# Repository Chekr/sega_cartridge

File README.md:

# sega_cartridge

NOTE: Part datasheets are NOT included with the license, and are included for reference use ONLY

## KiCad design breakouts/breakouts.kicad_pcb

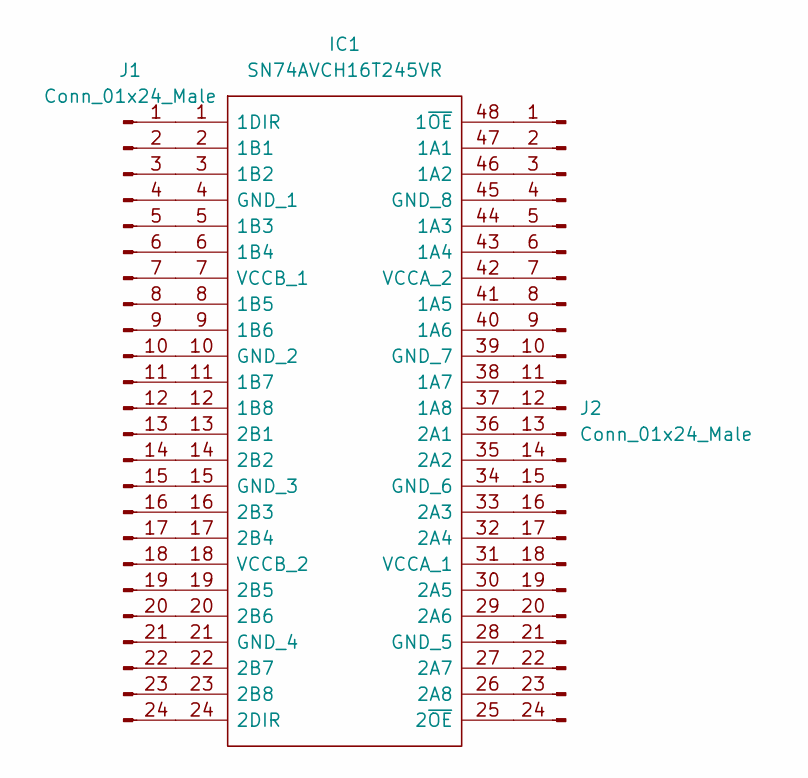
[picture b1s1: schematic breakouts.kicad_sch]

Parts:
IC1: SN74AVCH16T245VR; SOP40P640X120-48N; Manufacturer_Part_Number SN74AVCH16T245VR; Mouser Part Number 595-SN74AVCH16T245VR
J1, J2: Conn_01x24_Male; PinHeader_1x24_P2.54mm_Vertical

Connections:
unnamed: IC1.1 (1DIR), J1.1
unnamed: IC1.2 (1B1), J1.2
unnamed: IC1.3 (1B2), J1.3
unnamed: IC1.4 (GND_1), J1.4
unnamed: IC1.5 (1B3), J1.5
unnamed: IC1.6 (1B4), J1.6
unnamed: IC1.7 (VCCB_1), J1.7
unnamed: IC1.8 (1B5), J1.8
unnamed: IC1.9 (1B6), J1.9
unnamed: IC1.10 (GND_2), J1.10
unnamed: IC1.11 (1B7), J1.11
unnamed: IC1.12 (1B8), J1.12
unnamed: IC1.13 (2B1), J1.13
unnamed: IC1.14 (2B2), J1.14
unnamed: IC1.15 (GND_3), J1.15
unnamed: IC1.16 (2B3), J1.16
unnamed: IC1.17 (2B4), J1.17
unnamed: IC1.18 (VCCB_2), J1.18
unnamed: IC1.19 (2B5), J1.19
unnamed: IC1.20 (2B6), J1.20
unnamed: IC1.21 (GND_4), J1.21
unnamed: IC1.22 (2B7), J1.22
unnamed: IC1.23 (2B8), J1.23
unnamed: IC1.24 (2DIR), J1.24
unnamed: IC1.25 (2~OE), J2.24
unnamed: IC1.26 (2A8), J2.23
unnamed: IC1.27 (2A7), J2.22
unnamed: IC1.28 (GND_5), J2.21
unnamed: IC1.29 (2A6), J2.20
unnamed: IC1.30 (2A5), J2.19
unnamed: IC1.31 (VCCA_1), J2.18
unnamed: IC1.32 (2A4), J2.17
unnamed: IC1.33 (2A3), J2.16
unnamed: IC1.34 (GND_6), J2.15
unnamed: IC1.35 (2A2), J2.14
unnamed: IC1.36 (2A1), J2.13
unnamed: IC1.37 (1A8), J2.12
unnamed: IC1.38 (1A7), J2.11
unnamed: IC1.39 (GND_7), J2.10
unnamed: IC1.40 (1A6), J2.9
unnamed: IC1.41 (1A5), J2.8
unnamed: IC1.42 (VCCA_2), J2.7
unnamed: IC1.43 (1A4), J2.6
unnamed: IC1.44 (1A3), J2.5
unnamed: IC1.45 (GND_8), J2.4
unnamed: IC1.46 (1A2), J2.3
unnamed: IC1.47 (1A1), J2.2
unnamed: IC1.48 (1~OE), J2.1

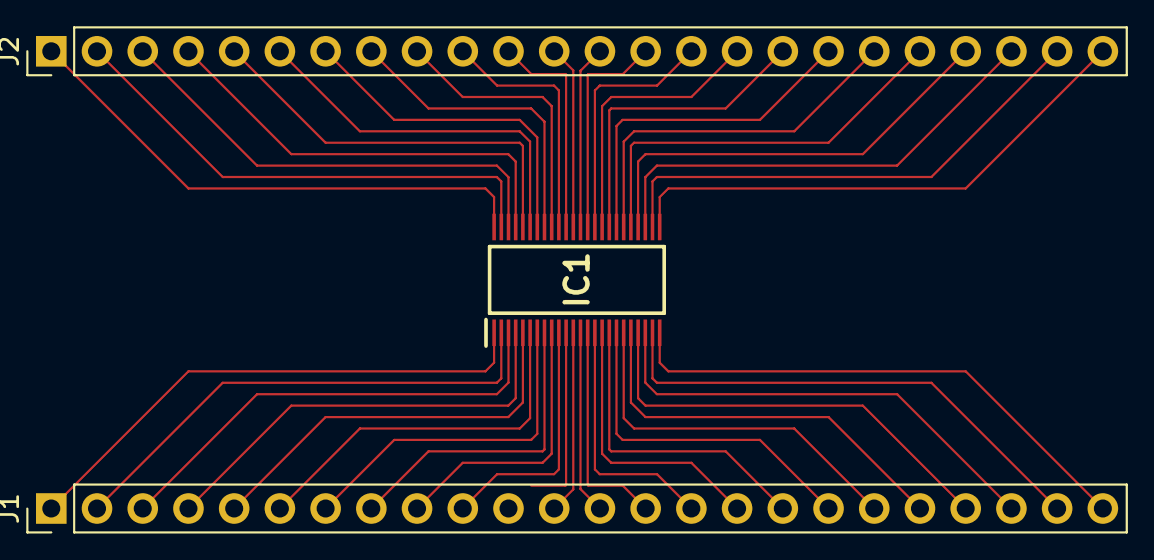
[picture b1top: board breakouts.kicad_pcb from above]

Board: 2 copper layers, 3 parts (0 on the bottom side), 48 nets.

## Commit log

2022-08-06 FIRST COMMIT
    Adding Docs and kicad files, no work yet
2022-08-06 More documentation
    removed old part datasheet (wrong voltage levels)
2022-08-06 More Datasheets+BOM
2022-08-20 Symbol updates, breakout board
    Made symbols for the level shifter and
    card edge connector. Started a breakout
    board for the level shifter.
2022-08-23 Putting traces on level shift breakout
